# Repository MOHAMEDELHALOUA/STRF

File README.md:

# STRF
The board incorporates an STM32 microcontroller, an RF transceiver, an antenna interface, and a micro-USB full-speed interface. It is designed for various projects, such as logging data from a robot with RF capabilities. The STM32 serves as a link between the RF transceiver and a host computer via USB, and the design emphasizes compactness, measuring 15mm in height and 40mm in length.

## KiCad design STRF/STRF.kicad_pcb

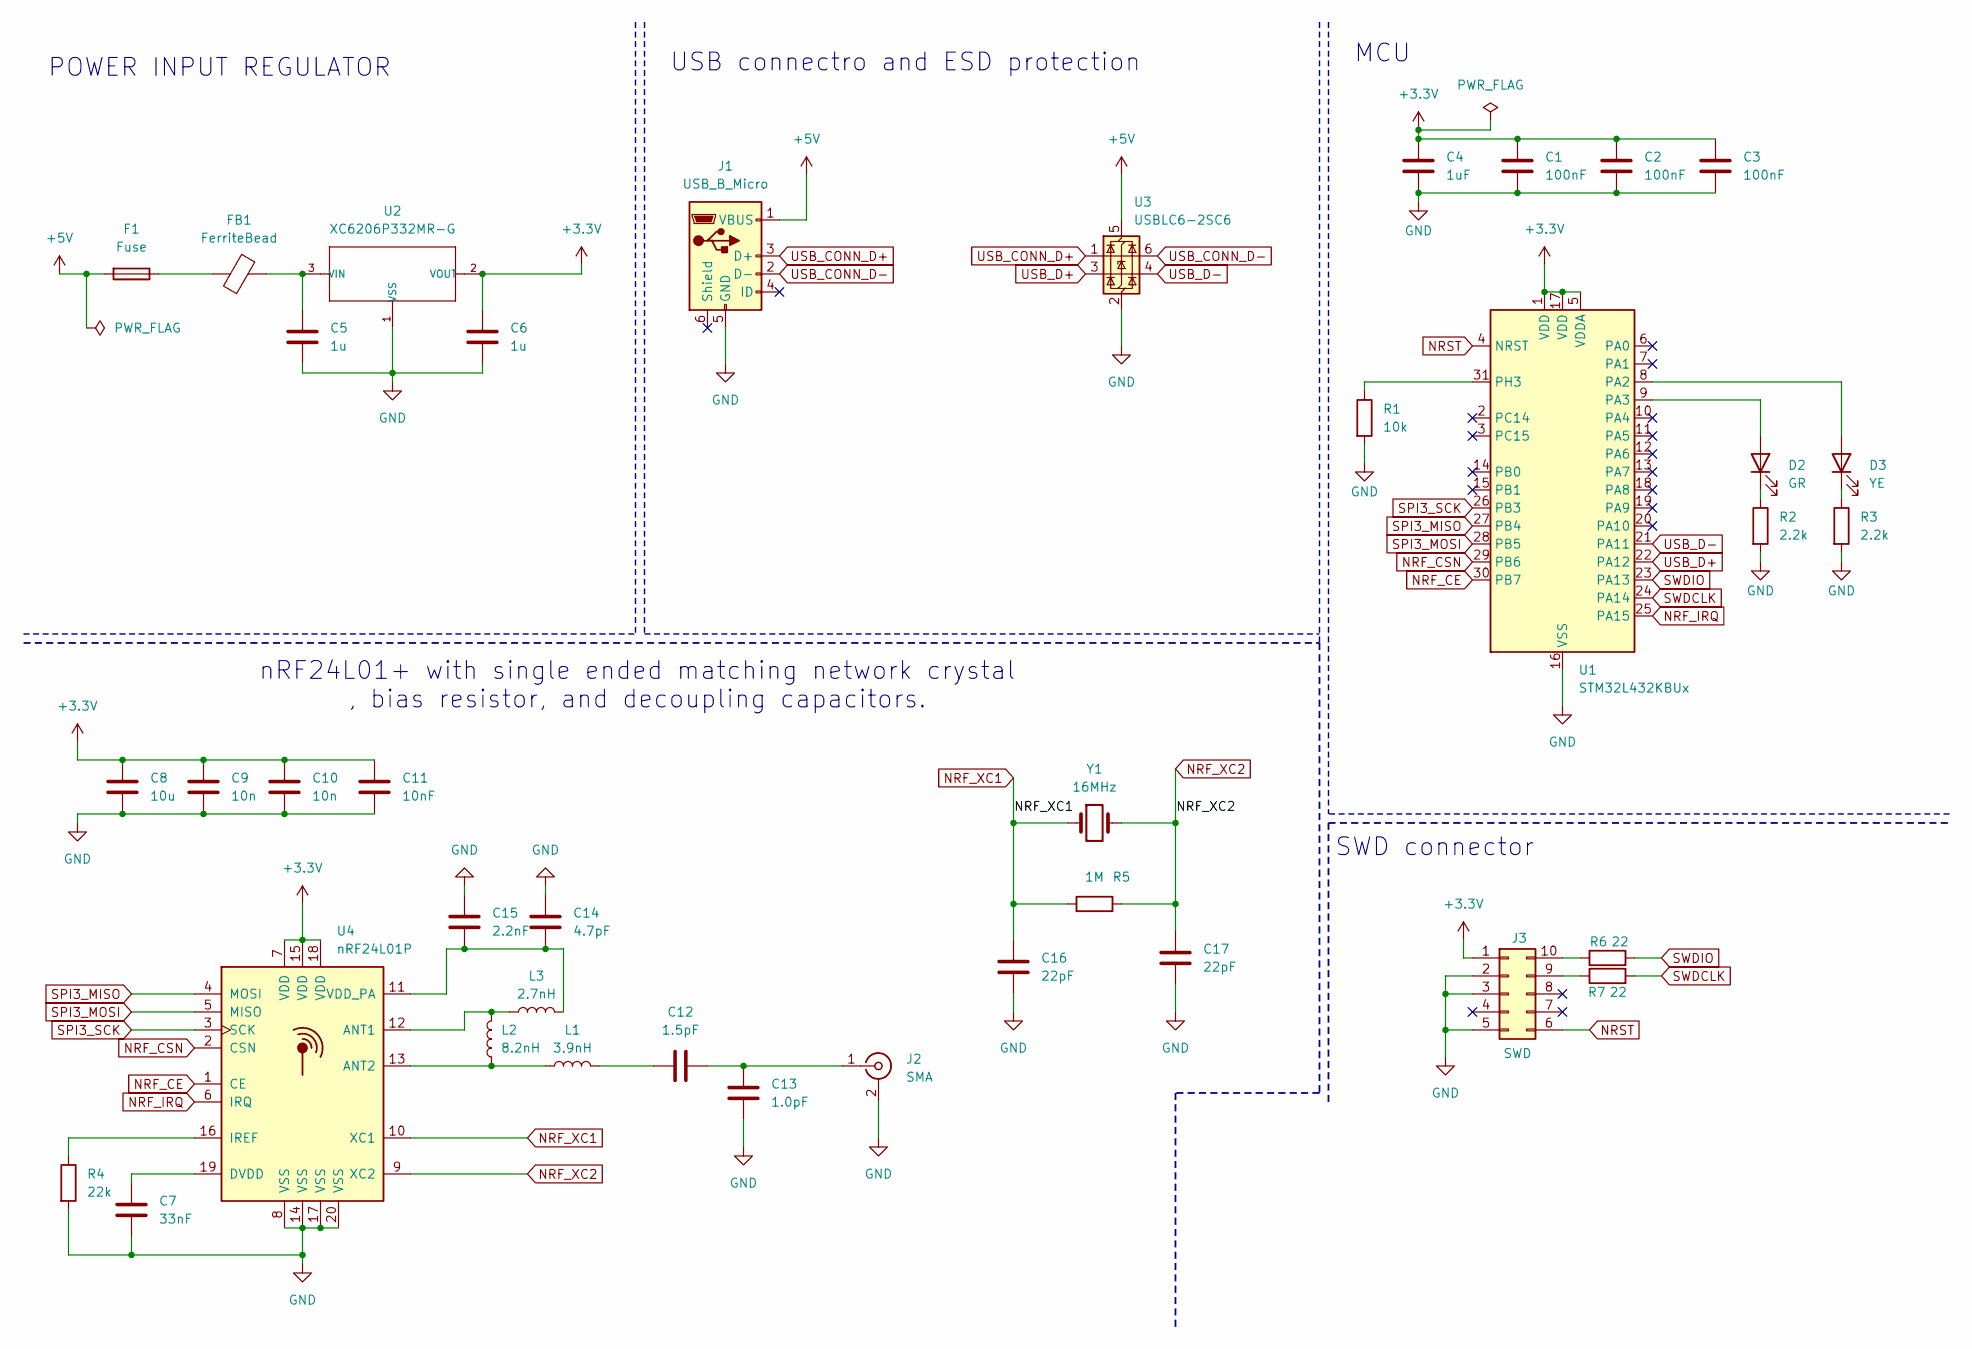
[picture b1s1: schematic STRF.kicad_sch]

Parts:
C1, C2, C3: 100nF; C_0402_1005Metric
C4: 1uF; C_1206_3216Metric
C5, C6: 1u; C_1206_3216Metric
C7: 33nF; C_0402_1005Metric
C8: 10u; C_1206_3216Metric
C9, C10: 10n; C_0402_1005Metric
C11: 10nF; C_0402_1005Metric
C12: 1.5pF; C_0402_1005Metric
C13: 1.0pF; C_0402_1005Metric
C14: 4.7pF; C_0402_1005Metric
C15: 2.2nF; C_0402_1005Metric
C16, C17: 22pF; C_0402_1005Metric
D2: GR; LED_0603_1608Metric
D3: YE; LED_0603_1608Metric
F1: Fuse; Fuse_0603_1608Metric
FB1: FerriteBead; L_0805_2012Metric
J1: USB_B_Micro; USB_Micro-B_Molex_47346-0001
J2: SMA; SMA_Amphenol_132289_EdgeMount
J3: SWD; PinHeader_2x05_P1.00mm_Vertical_SMD
L1: 3.9nH; L_0201_0603Metric
L2: 8.2nH; L_0201_0603Metric
L3: 2.7nH; L_01005_0402Metric
R1: 10k; R_0402_1005Metric
R2, R3: 2.2k; R_0603_1608Metric
R4: 22k; R_0612_1632Metric
R5: 1M; R_1210_3225Metric
R6, R7: 22; R_0603_1608Metric
U1: STM32L432KBUx; QFN-32-1EP_5x5mm_P0.5mm_EP3.45x3.45mm
U2: XC6206P332MR-G; SOT-23; MPN XC6206P332MR-G
U3: USBLC6-2SC6; SOT-23-6
U4: nRF24L01P; QFN-20-1EP_4x4mm_P0.5mm_EP2.5x2.5mm
Y1: 16MHz; Crystal_SMD_0603-2Pin_6.0x3.5mm

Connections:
+3.3V: C1.1, C2.1, C3.1, C4.1, C6.1, C8.1, C9.1, C10.1, C11.1, J3.1, U1.1 (VDD), U1.5 (VDDA), U1.17 (VDD), U2.2 (VOUT), U4.7 (VDD), U4.15 (VDD), U4.18 (VDD)
+5V: F1.2, J1.1 (VBUS), U3.5 (VBUS)
GND: C1.2, C2.2, C3.2, C4.2, C5.2, C6.2, C7.2, C8.2, C9.2, C10.2, C11.2, C13.1, C14.2, C15.2, C16.2, C17.2, J1.5 (GND), J2.2 (Ext), J3.2, J3.3, J3.5, R1.2, R2.2, R3.2, R4.2, U1.16 (VSS), U1.32 (VSS), U1.33 (VSS), U2.1 (VSS), U3.2 (GND), U4.8 (VSS), U4.14 (VSS), U4.17 (VSS), U4.20 (VSS)
NRF_CE: U1.30 (PB7), U4.1 (CE)
NRF_CSN: U1.29 (PB6), U4.2 (CSN)
NRF_IRQ: U1.25 (PA15), U4.6 (IRQ)
NRF_XC1: C16.1, R5.1, U4.10 (XC1), Y1.1
NRF_XC2: C17.1, R5.2, U4.9 (XC2), Y1.2
NRST: J3.6, U1.4 (NRST)
unnamed: C12.1, L1.2
unnamed: D2.2 (A), U1.9 (PA3)
unnamed: D2.1 (K), R2.1
unnamed: D3.2 (A), U1.8 (PA2)
unnamed: D3.1 (K), R3.1
unnamed: F1.1, FB1.1
unnamed: C12.2, C13.2, J2.1 (In)
unnamed: J3.9, R7.1
unnamed: J3.10, R6.1
unnamed: R1.1, U1.31 (PH3)
unnamed: C5.1, FB1.2, U2.3 (VIN)
unnamed: L2.2, L3.1, U4.12 (ANT1)
unnamed: L1.1, L2.1, U4.13 (ANT2)
unnamed: C7.1, U4.19 (DVDD)
unnamed: R4.1, U4.16 (IREF)
unnamed: C14.1, C15.1, L3.2, U4.11 (VDD_PA)
SPI3_MISO: U1.27 (PB4), U4.4 (MOSI)
SPI3_MOSI: U1.28 (PB5), U4.5 (MISO)
SPI3_SCK: U1.26 (PB3), U4.3 (SCK)
SWDCLK: R7.2, U1.24 (PA14)
SWDIO: R6.2, U1.23 (PA13)
USB_CONN_D+: J1.3 (D+), U3.1 (I/O1)
USB_CONN_D-: J1.2 (D-), U3.6 (I/O1)
USB_D+: U1.22 (PA12), U3.3 (I/O2)
USB_D-: U1.21 (PA11), U3.4 (I/O2)

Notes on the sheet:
POWER INPUT REGULATOR
SWD connector
nRF24L01+ with single ended matching network crystal , bias resistor, and decoupling capacitors.
USB connectro and ESD protection
MCU

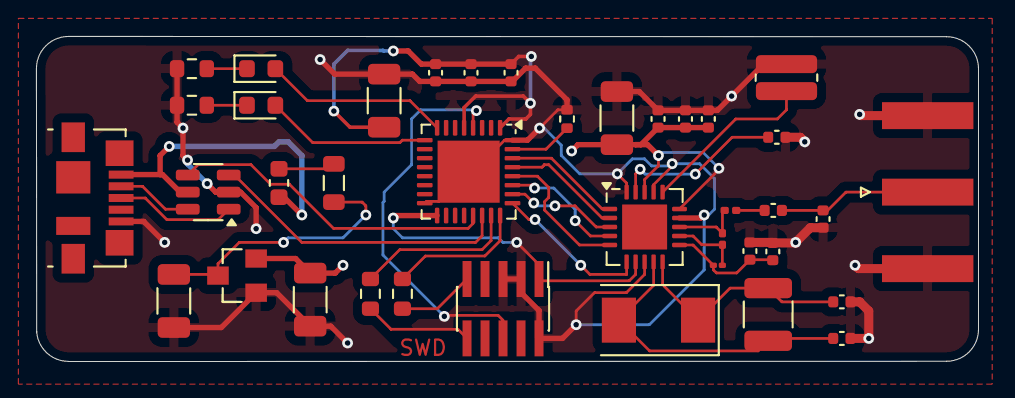
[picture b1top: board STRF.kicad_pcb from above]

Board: 2 copper layers, 52.3 x 18.1 mm, 39 parts (0 on the bottom side), 34 nets.

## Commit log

2025-02-25 this is an RF board based on the stm32 mcu and nrf24l01p
2025-02-25 just adding a small description of the board
2025-11-02 Update USB interface description in README
